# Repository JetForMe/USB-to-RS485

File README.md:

# High Speed USB to EIA-485 Adapter

I got fed up trying to find a USB-to-EIA485 adapter that could do 4 Mbps or better. Most
of the available FTDI and CP2102N ICs top out at 3 Mbps, and most of the available
EIA-485 driver ICs are slew rate-limited to well below 4 Mbps.

So I’ve created this adapter. Some of its features include:

* USB-C
* 12 Mbps maximum speed
* 5 V, 3 A power output
* 3.3 V, 600 mA (including the adapter itself) power output
* Configurable USB-C PD output, up to 20 V @ 100 W (hopefully)
* FTDI-compatible 3.3 V 6-pin UART header (5V tolerant)
* 3.3 V or 5 V selectable, ±70V fault-protected EIA-485 driver (PROFIBUS compatible)
* Full- or half-duplex operation
* Optional bus termination resistors
* EIA-485A and EIA-422B compatible
* JTAG programmer/debugger
* Interface to many other serial busses (I2C, SPI, etc.)
* All FT232HP GPIO pins brought out on headers

[Schematic](/hardware/RS-485.pdf)

## To Do

So much still to do!

* Add 5 V, 3 A buck regulator
* Add 3.3V linear regulator
* Add EEPROM
* Decoupling caps!
* Connect RESET and PWRSAV
* Remove voltage selector from FTDI header? We can't do 5V IO on it, although I think it’s 5V-tolerant.
* PCB layout
* Change schematic PDF generation to happen on push, if possible.

## macOS Notes

To set non-standard UART speeds on macOS, you must use `ioctl()` after calling `tcsetattr()`:

In C/C++:

```cpp
#include <sys/ioctl.h>
#include <termios.h>

#define IOSSIOSPEED _IOW('T', 2, speed_t)		//	Defined in <IOKit/serial/ioss.h>
speed_t speed = 4000000;
if (ioctl(fd, IOSSIOSPEED, &speed) != 0)
{
    perror(__FILE__ ":" STRINGIZE(__LINE__) ": ioctl set speed");
}
```

From [IOSerialTestLib.c](https://opensource.apple.com/source/IOSerialFamily/IOSerialFamily-74/tests/IOSerialTestLib.c):

```c
int _testIOSSIOSPEEDIoctl(int fd, speed_t speed)
{
    struct termios options;
    
    // The IOSSIOSPEED ioctl can be used to set arbitrary baud rates other than
    // those specified by POSIX. The driver for the underlying serial hardware
    // ultimately determines which baud rates can be used. This ioctl sets both
    // the input and output speed.
    
    if (ioctl(fd, IOSSIOSPEED, &speed) == -1) {
        printf("[WARN] ioctl(..., IOSSIOSPEED, %lu).\n", speed);
        goto fail;
    }
    
    // Check that speed is properly modified
    if (tcgetattr(fd, &options) == -1) {
        printf("[WARN] _modifyAttributes: tcgetattr failed\n");
        goto fail;
    }
    
    if (cfgetispeed(&options) != speed ||
        cfgetospeed(&options) != speed) {
        printf("[WARN] _modifyAttributes: cfsetspeed failed, %lu, %lu.\n",
               speed,
               cfgetispeed(&options));
        goto fail;
    }
    
    return 0;
fail:
    return -1;
}
```

Swift version to come! (_IOW defined in <sys/ioccom.h>)

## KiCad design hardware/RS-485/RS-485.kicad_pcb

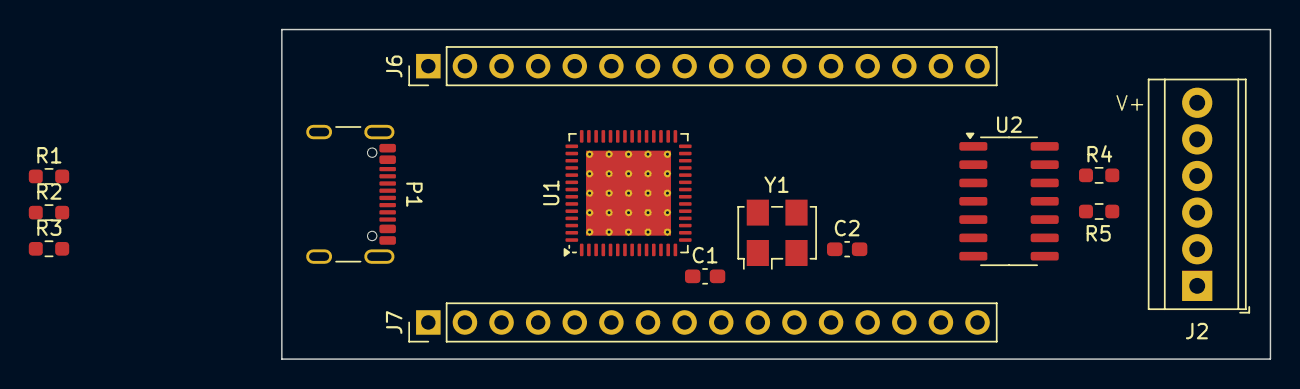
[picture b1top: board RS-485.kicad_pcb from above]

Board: 4 copper layers, 68.6 x 22.9 mm, 14 parts (0 on the bottom side), 39 nets, no tracks yet.

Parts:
C1, C2: 18pF; C_0603_1608Metric_Pad1.08x0.95mm_HandSolder
J2: Screw_Terminal_01x06; TerminalBlock_TE_282834-6_1x06_P2.54mm_Horizontal
J6, J7: Conn_01x16_Pin; PinHeader_1x16_P2.54mm_Vertical
P1: USB_C_Plug_USB2.0; USB_C_Receptacle_GCT_USB4105-xx-A_16P_TopMnt_Horizontal
R1: 12kΩ 1%; R_0603_1608Metric_Pad0.98x0.95mm_HandSolder
R2, R3: 200Ω; R_0603_1608Metric_Pad0.98x0.95mm_HandSolder
R4, R5: 120Ω; R_0603_1608Metric_Pad0.98x0.95mm_HandSolder
U1: FT232HP; QFN-56-1EP_8x8mm_P0.5mm_EP5.9x5.9mm_ThermalVias
U2: SOIC-14_3.9x8.7mm_P1.27mm
Y1: LFXTAL055999; Oscillator_SMD_TXC_7C-4Pin_5.0x3.2mm_HandSoldering

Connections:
+3.3V: J7.6, U1.5 (VCCIO), U1.13 (VCCIO), U1.14 (VCCIO), U1.18 (VREGIN), U1.28 (VCCIO), U1.40 (VCCIO), U1.47 (VCC_USB), U1.51 (VCC_PD), U1.54 (PD1_VCONN), U2.1 (Vio), U2.8 (SLR)
+5V: J7.4, J7.5, U2.14 (Vcc)
/AC0: J6.3, U1.32 (AC0), U2.3 (~RE), U2.4 (DE)
/AC1: J6.4, U1.33 (AC1)
/AC2: J6.5, U1.34 (AC2)
/AC3: J6.6, R3.2, U1.35 (AC3)
/AC4: J6.7, R2.2, U1.37 (AC4)
/AC5: J6.8, U1.38 (AC5)
/AC6: J6.9, U1.39 (AC6)
/AC7: J6.10, U1.42 (AC7)
/AC8: J6.11, U1.43 (AC8)
/AC9: J6.12, U1.44 (AC9)
/AD0: J7.13, U1.23 (AD0), U2.5 (D)
/AD1: J7.12, U1.24 (AD1), U2.2 (R)
/AD2: J7.11, U1.25 (AD2)
/AD3: J7.15, U1.26 (AD3)
/AD4: J7.7, U1.27 (AD4)
/AD5: J7.8, U1.29 (AD5)
/AD6: J7.9, U1.30 (AD6)
/AD7: J7.10, U1.31 (AD7)
/D+: P1.A6 (D+), P1.B6 (D+), U1.49 (DP)
/D-: P1.A7 (D-), P1.B7 (D-), U1.48 (DM)
/GPIO0: J6.13, U1.7 (GPIO0)
/GPIO1: J6.14, U1.8 (GPIO1)
/GPIO2: J6.15, U1.9 (GPIO2)
/GPIO3: J6.16, U1.10 (GPIO3)
GND: C1.2, C2.2, J2.1, J6.1, J6.2, J7.1, J7.16, P1.A1 (GND), P1.A12 (GND), P1.B1 (GND), P1.B12 (GND), P1.S1 (SHIELD), R1.1, U1.4 (TEST), U1.12 (GND), U1.17 (GND), U1.21 (GND), U2.6 (Gnd)
unnamed: J2.2, R4.1, U2.9 (Y)
unnamed: J2.3, R4.2, U2.10 (Z)
unnamed: J2.4, R5.1, U2.11 (B)
unnamed: J2.5, R5.2, U2.12 (A)
unnamed: P1.A5 (CC1), U1.55 (PD1_CC1)
unnamed: P1.B5 (CC2), U1.52 (PD1_CC2)
unnamed: U1.11 (VCORE), U1.19 (VREGOUT), U1.22 (VCORE), U1.36 (VCORE), U1.46 (VCORE), U1.56 (VCORE)
unnamed: P1.A4 (VBUS), P1.A9 (VBUS), P1.B4 (VBUS), P1.B9 (VBUS), U1.53 (PD1_SVBUS)
unnamed: C1.1, U1.15 (OSCI), Y1.1
unnamed: C2.1, U1.16 (OSCO), Y1.2
unnamed: R1.2, U1.50 (REF)
VUSB: J7.2, J7.3

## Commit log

2024-06-23 First checkin.
2024-06-23 Added PDF of schematic.
2024-06-23 Added README, gitignore.
2024-06-23 Added info to title block.
2024-06-23 More README notes.
2024-06-23 Added TVS diodes to CC and D+/- lines
2024-06-23 Testing pre-commit hook
2024-06-23 Updated readme for new schematic PDF file name
2024-06-23 Updated readme and title block.
2024-06-25 Added todo for decoupling caps
